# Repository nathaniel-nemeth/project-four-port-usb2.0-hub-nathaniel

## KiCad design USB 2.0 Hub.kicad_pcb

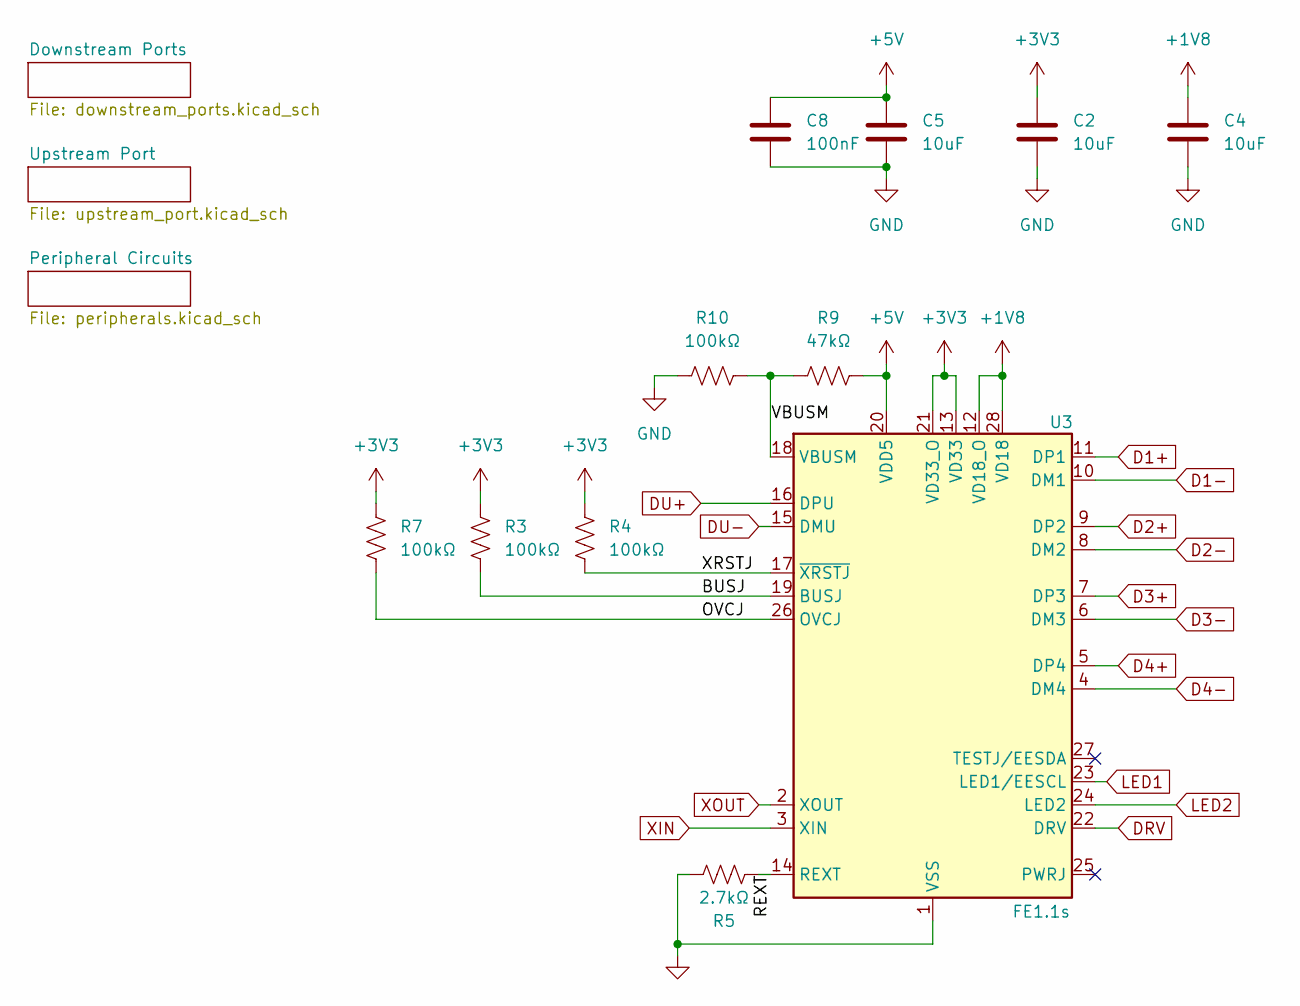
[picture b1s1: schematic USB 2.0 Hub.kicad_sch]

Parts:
C2, C4, C5: 10uF; C_0805_2012Metric_Pad1.18x1.45mm_HandSolder
C8: 100nF; C_0805_2012Metric_Pad1.18x1.45mm_HandSolder
R3, R4, R7, R10: 100kΩ; R_0805_2012Metric_Pad1.20x1.40mm_HandSolder
R5: 2.7kΩ; R_0805_2012Metric_Pad1.20x1.40mm_HandSolder
R9: 47kΩ; R_0805_2012Metric_Pad1.20x1.40mm_HandSolder
U3: FE1.1s; SSOP-28_3.9x9.9mm_P0.635mm

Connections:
+1V8: C4.1, U3.12 (VD18_O), U3.28 (VD18)
+3V3: C2.1, R3.1, R4.1, R7.1, U3.13 (VD33), U3.21 (VD33_O)
/BUSJ: R3.2, U3.19 (BUSJ)
/OVCJ: R7.2, U3.26 (OVCJ)
/REXT: R5.2, U3.14 (REXT)
/VBUSM: R9.1, R10.2, U3.18 (VBUSM)
/XRSTJ: R4.2, U3.17 (~XRSTJ)
D1+: U3.11 (DP1); also elsewhere on the board
D1-: U3.10 (DM1); also elsewhere on the board
D2+: U3.9 (DP2); also elsewhere on the board
D2-: U3.8 (DM2); also elsewhere on the board
D4+: U3.5 (DP4); also elsewhere on the board
D4-: U3.4 (DM4); also elsewhere on the board
DRV: U3.22 (DRV); also elsewhere on the board
DU+: U3.16 (DPU); also elsewhere on the board
DU-: U3.15 (DMU); also elsewhere on the board
GND: C2.2, C4.2, C5.2, C8.2, R5.1, R10.1, U3.1 (VSS); also elsewhere on the board
LED1: U3.23 (LED1/EESCL); also elsewhere on the board
LED2: U3.24 (LED2); also elsewhere on the board
XIN: U3.3 (XIN); also elsewhere on the board
XOUT: U3.2 (XOUT); also elsewhere on the board

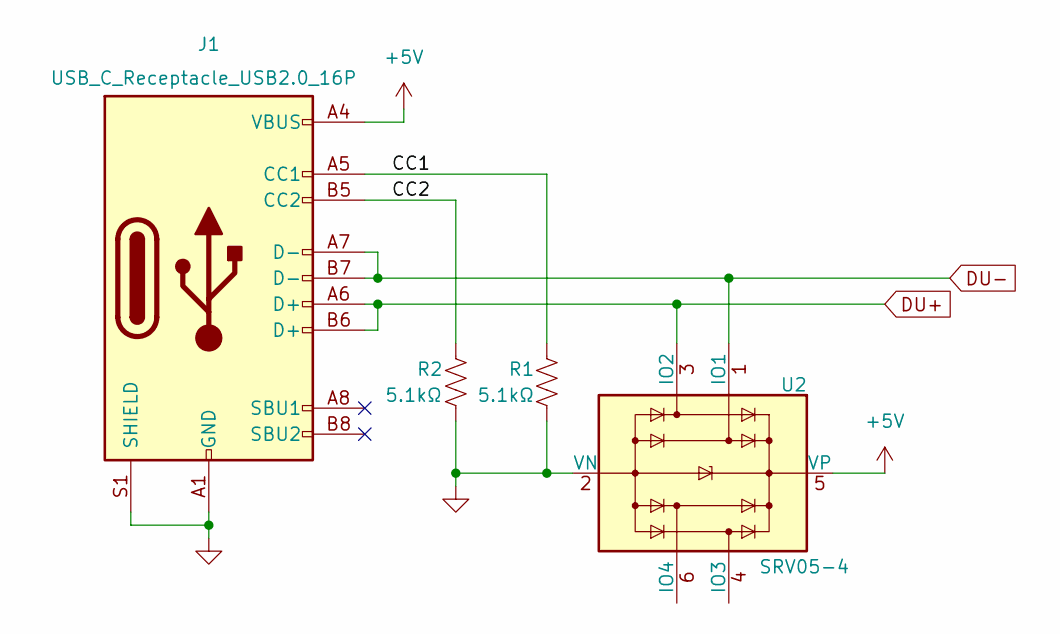
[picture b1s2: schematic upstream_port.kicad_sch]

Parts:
J1: USB_C_Receptacle_USB2.0_16P; USB_C_Receptacle_G-Switch_GT-USB-7010ASV
R1, R2: 5.1kΩ; R_0805_2012Metric_Pad1.20x1.40mm_HandSolder
U2: SRV05-4; SOT-23-6

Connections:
/Upstream Port/CC1: J1.A5 (CC1), R1.2
/Upstream Port/CC2: J1.B5 (CC2), R2.2
DU+: J1.A6 (D+), J1.B6 (D+), U2.3 (IO2); also elsewhere on the board
DU-: J1.A7 (D-), J1.B7 (D-), U2.1 (IO1); also elsewhere on the board
GND: J1.A1 (GND), J1.A12 (GND), J1.B1 (GND), J1.B12 (GND), J1.S1 (SHIELD), R1.1, R2.1, U2.2 (VN); also elsewhere on the board

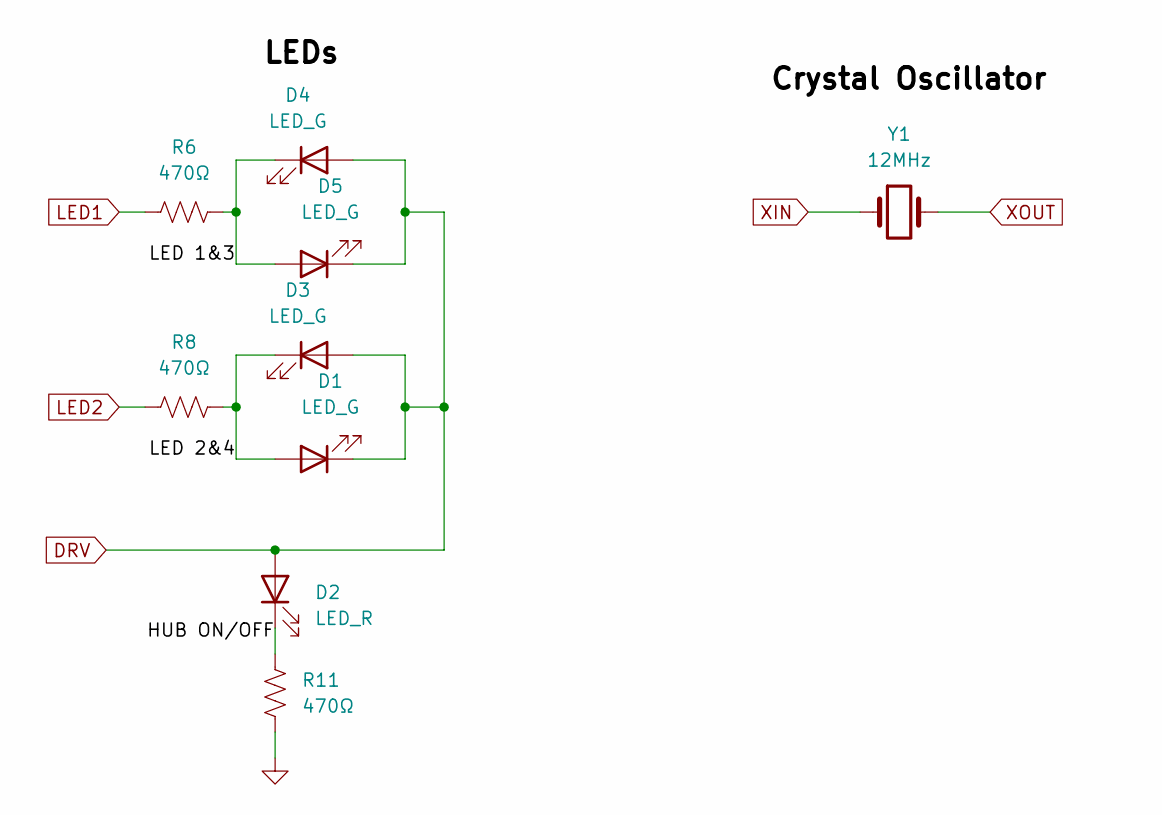
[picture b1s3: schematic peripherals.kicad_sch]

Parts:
D1, D3, D4, D5: LED_G; LED_0805_2012Metric_Pad1.15x1.40mm_HandSolder
D2: LED_R; LED_0805_2012Metric_Pad1.15x1.40mm_HandSolder
R6, R8, R11: 470Ω; R_0805_2012Metric_Pad1.20x1.40mm_HandSolder
Y1: 12MHz; Crystal_HC49-U_Vertical

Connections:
/Peripheral Circuits/HUB ON/OFF: D2.1 (K), R11.2
/Peripheral Circuits/LED 1&3: D4.1 (K), D5.2 (A), R6.2
/Peripheral Circuits/LED 2&4: D1.2 (A), D3.1 (K), R8.2
DRV: D1.1 (K), D2.2 (A), D3.2 (A), D4.2 (A), D5.1 (K); also elsewhere on the board
GND: R11.1; also elsewhere on the board
LED1: R6.1; also elsewhere on the board
LED2: R8.1; also elsewhere on the board
XIN: Y1.1; also elsewhere on the board
XOUT: Y1.2; also elsewhere on the board

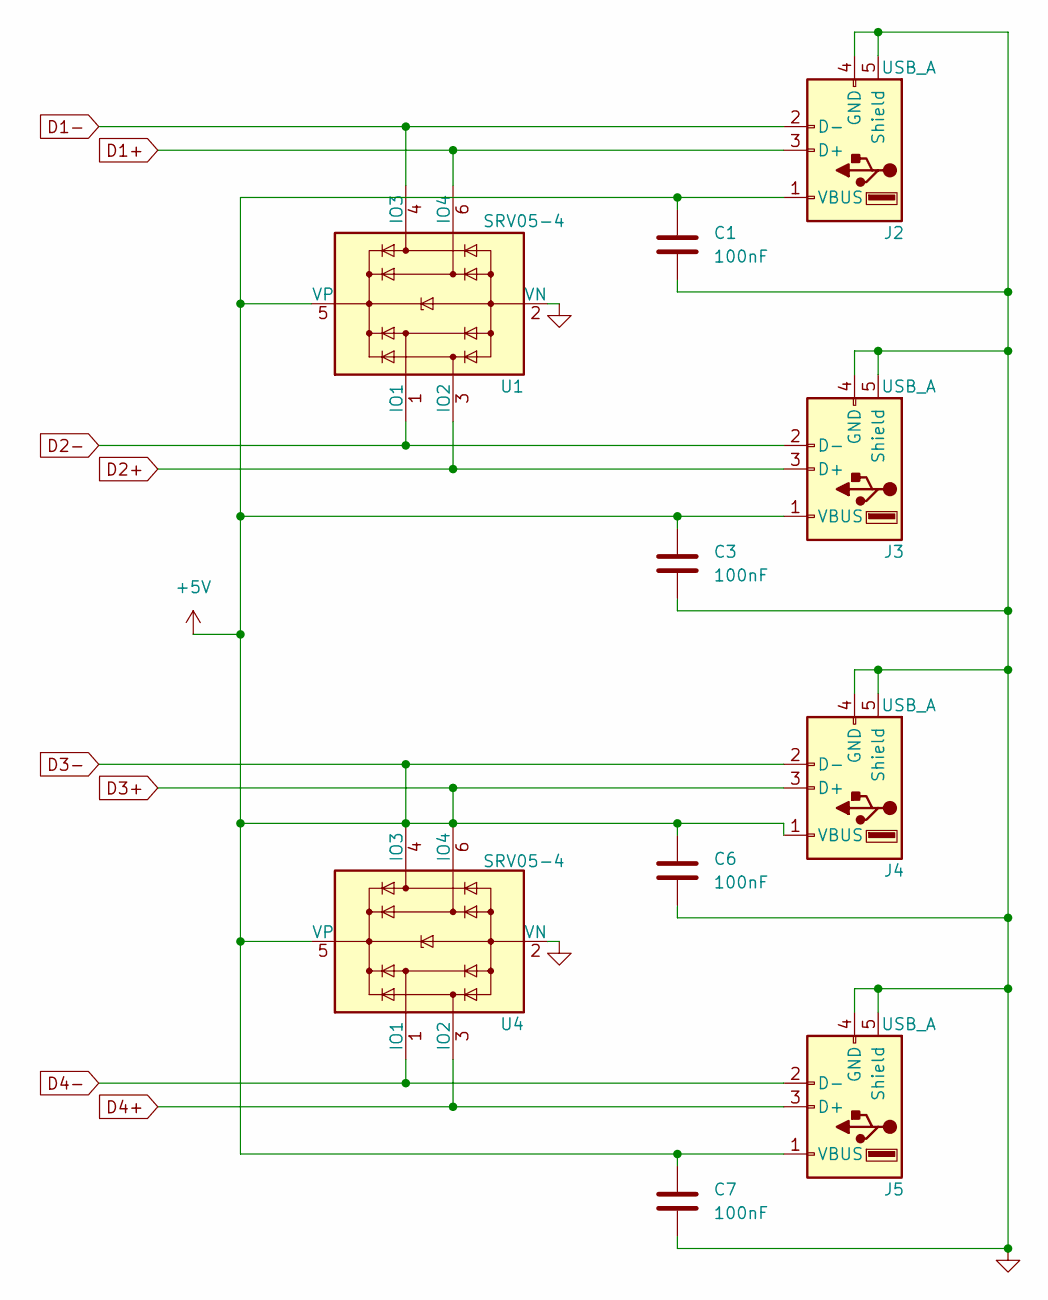
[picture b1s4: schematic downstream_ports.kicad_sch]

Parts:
C1, C3, C6, C7: 100nF; C_0805_2012Metric_Pad1.18x1.45mm_HandSolder
J2, J3, J4, J5: USB_A; USB_A_Stewart_SS-52100-001_Horizontal
U1, U4: SRV05-4; SOT-23-6

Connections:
D1+: J2.3 (D+), U1.6 (IO4); also elsewhere on the board
D1-: J2.2 (D-), U1.4 (IO3); also elsewhere on the board
D2+: J3.3 (D+), U1.3 (IO2); also elsewhere on the board
D2-: J3.2 (D-), U1.1 (IO1); also elsewhere on the board
D4+: J5.3 (D+), U4.3 (IO2); also elsewhere on the board
D4-: J5.2 (D-), U4.1 (IO1); also elsewhere on the board
GND: C1.2, C3.2, C6.2, C7.2, J2.4 (GND), J2.5 (Shield), J3.4 (GND), J3.5 (Shield), J4.4 (GND), J4.5 (Shield), J5.4 (GND), J5.5 (Shield), U1.2 (VN), U4.2 (VN); also elsewhere on the board

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
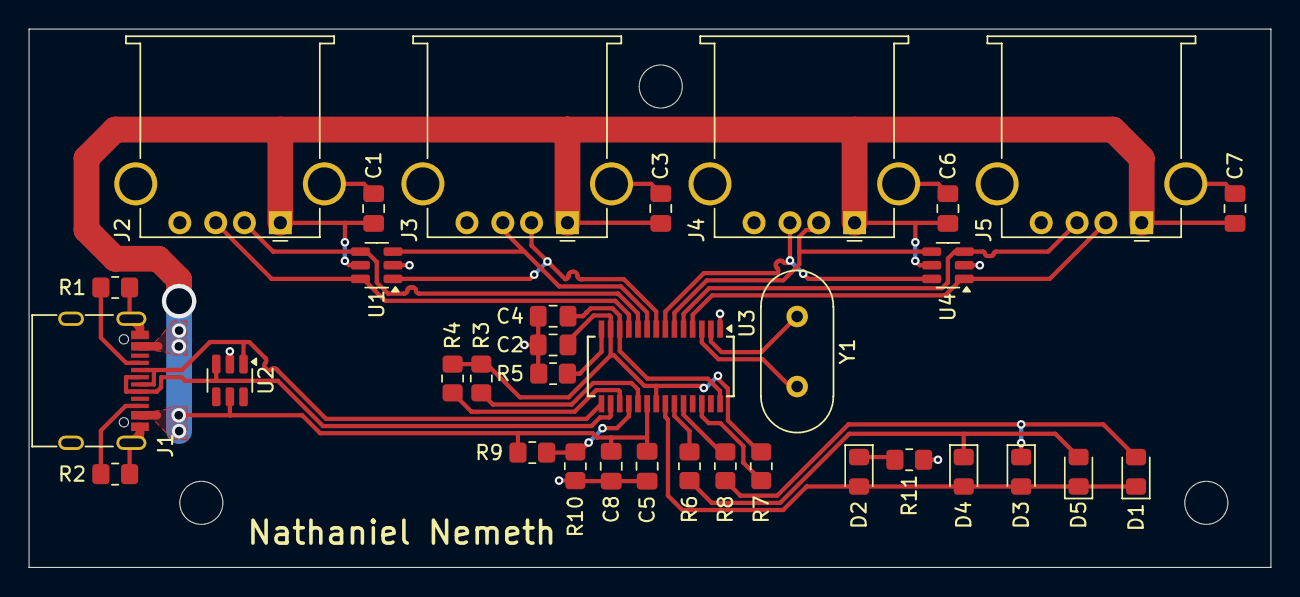
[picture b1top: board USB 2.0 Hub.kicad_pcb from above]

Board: 2 copper layers, 86.5 x 37.5 mm, 34 parts (0 on the bottom side), 29 nets.

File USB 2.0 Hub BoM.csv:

"Id";"Designator";"Footprint";"Quantity";"Designation";"Supplier and ref";
1;"U1,U4,U2";"SOT-23-6";3;"SRV05-4";;;
2;"J5,J3,J2,J4";"USB_A_Stewart_SS-52100-001_Horizontal";4;"USB_A";;;
3;"Y1";"Crystal_HC49-U_Vertical";1;"12MHz";;;
4;"R11,R6,R8";"R_0805_2012Metric_Pad1.20x1.40mm_HandSolder";3;"470Ω";;;
5;"R2,R1";"R_0805_2012Metric_Pad1.20x1.40mm_HandSolder";2;"5.1kΩ";;;
6;"R4,R7,R3,R10";"R_0805_2012Metric_Pad1.20x1.40mm_HandSolder";4;"100kΩ";;;
7;"C1,C6,C3,C7";"C_0805_2012Metric_Pad1.18x1.45mm_HandSolder";4;"0.1uF";;;
8;"C5,C2,C4";"C_0805_2012Metric_Pad1.18x1.45mm_HandSolder";3;"10uF";;;
9;"J1";"USB_C_Receptacle_G-Switch_GT-USB-7010ASV";1;"USB_C_Receptacle_USB2.0_16P";;;
10;"C8";"C_0805_2012Metric_Pad1.18x1.45mm_HandSolder";1;"100nF";;;
11;"R5";"R_0805_2012Metric_Pad1.20x1.40mm_HandSolder";1;"2.7kΩ";;;
12;"D1,D3,D4,D5";"LED_0805_2012Metric_Pad1.15x1.40mm_HandSolder";4;"LED_G";;;
13;"U3";"SSOP-28_3.9x9.9mm_P0.635mm";1;"FE1.1s";;;
14;"D2";"LED_0805_2012Metric_Pad1.15x1.40mm_HandSolder";1;"LED_R";;;
15;"R9";"R_0805_2012Metric_Pad1.20x1.40mm_HandSolder";1;"47kΩ";;;

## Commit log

2024-11-25 Initializing Git in project directory and adding files
2024-11-26 Added finishing touches to final design and generated BoM
